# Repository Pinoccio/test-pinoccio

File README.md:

pinoccio-test-harness
=====================

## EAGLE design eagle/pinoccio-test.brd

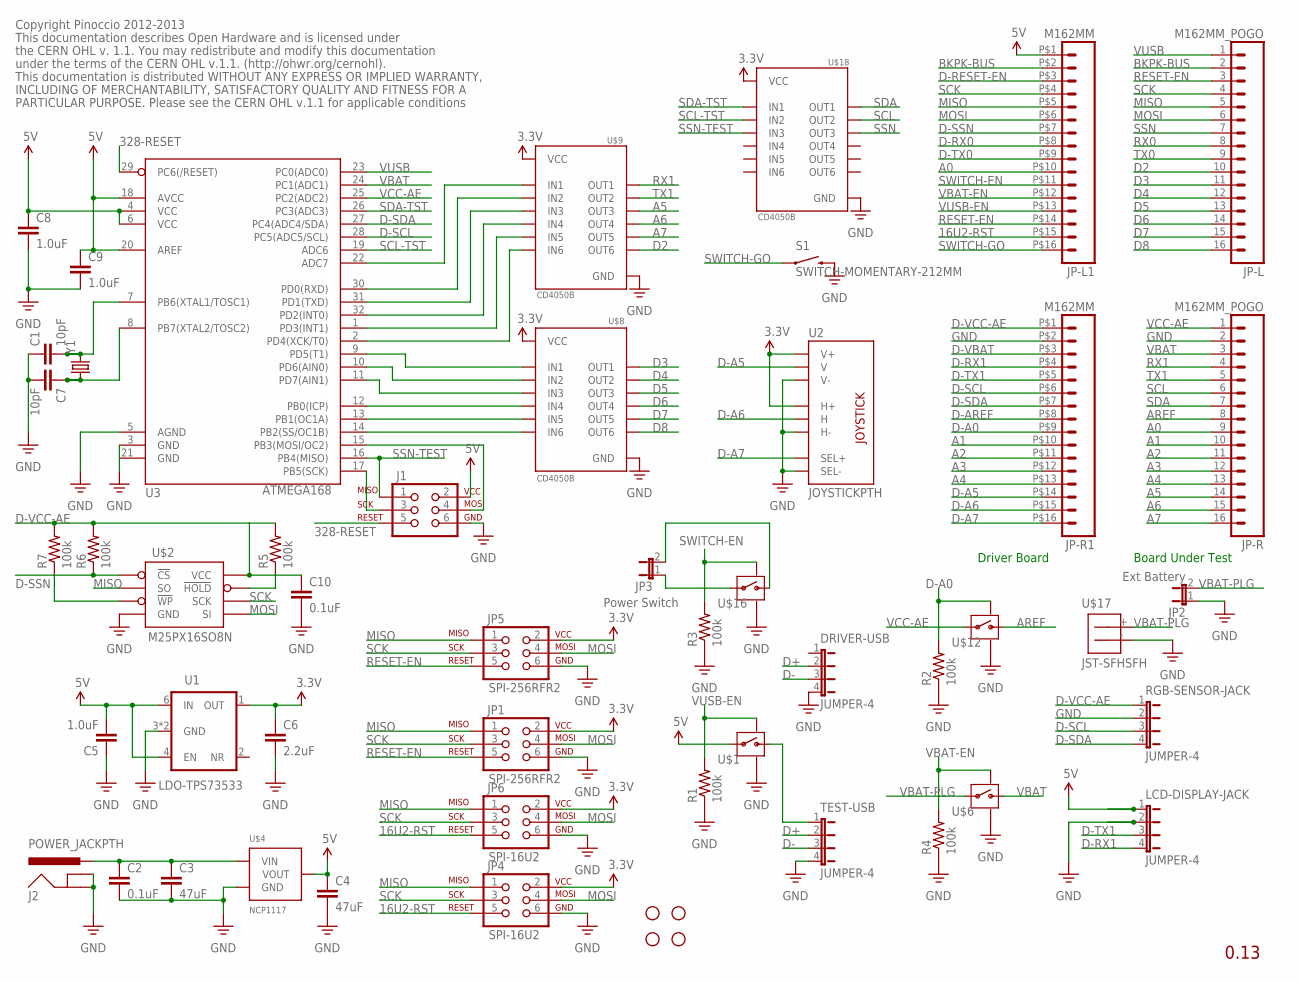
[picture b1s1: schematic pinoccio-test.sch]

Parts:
C1, C7: 10pF; 0402-CAP
C2, C10: 0.1uF; 0402-CAP
C3, C4: 47uF; 0805
C5, C8, C9: 1.0uF; 0402-CAP
C6: 2.2uF; 0402-CAP
DRIVER-USB: JUMPER-4; 1X04
J1: SPI-328P; 2X3
J2: POWER_JACKPTH; POWER_JACK_PTH
JP1, JP5: SPI-256RFR2; 2X3
JP2: Ext Battery; 1X02
JP3: Power Switch; 1X02
JP4, JP6: SPI-16U2; 2X3
JP7, JP9, JP10, JP12: STAND-OFF
JP-L: M162MM_POGO; 1X16_2MM_POGO
JP-L1: M162MM; 1X16_2MM
JP-R: M162MM_POGO; 1X16_2MM_POGO
JP-R1: M162MM; 1X16_2MM
LCD-DISPLAY-JACK: JUMPER-4; 1X04
R1, R2, R3, R4, R5, R6, R7: 100k; 0402-RES
RGB-SENSOR-JACK: JUMPER-4; 1X04
S1: SWITCH-MOMENTARY-212MM; TACTILE-PTH-12MM
TEST-USB: JUMPER-4; 1X04
U1: LDO-TPS73533; SON-6-DRV
U2: JOYSTICKPTH; JOYSTICK
U3: ATMEGA168; TQFP32-08
U$1, U$6, U$12, U$16: SWITCH-MOSFETTDFN4; TDFN4
U$2: M25PX16SO8N; SO8N
U$4: NCP1117; SOT223
U$8, U$9, U$18: CD4050B; TSSOP-16
U$17: JST-SFHSFH; JST-SFH
Y1: CRYSTALABM10; CRYSTAL-SMD-2.5X2-ABM10

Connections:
3.3V: C6.1, JP1.2, JP4.2, JP5.2, JP6.2, U1.1 (OUT), U2.H1 (H+), U2.V1 (V+), U$8.1 (VCC), U$9.1 (VCC), U$18.1 (VCC)
5V: C4.1, C5.2, C8.1, C9.1, J1.2, JP-L1.P$1 (1), LCD-DISPLAY-JACK.1, U1.4 (EN), U1.6 (IN), U3.4 (VCC), U3.6 (VCC), U3.18 (AVCC), U3.20 (AREF), U$1.P$3 (IN), U$4.2 (VOUT), U$4.4 (VOUT)
16U2-RST: JP4.5, JP6.5, JP-L1.P$15 (15)
328-RESET: J1.5, U3.29 (PC6(/RESET))
A0: JP-L1.P$10 (10), JP-R.9
A1: JP-R.10, JP-R1.P$10 (10)
A2: JP-R.11, JP-R1.P$11 (11)
A3: JP-R.12, JP-R1.P$12 (12)
A4: JP-R.13, JP-R1.P$13 (13)
A5: JP-R.14, U$9.6 (OUT3)
A6: JP-R.15, U$9.10 (OUT4)
A7: JP-R.16, U$9.12 (OUT5)
AREF: JP-R.8, U$12.P$1 (OUT)
BKPK-BUS: JP-L.2, JP-L1.P$2 (2)
D2: JP-L.10, U$9.15 (OUT6)
D3: JP-L.11, U$8.2 (OUT1)
D4: JP-L.12, U$8.4 (OUT2)
D5: JP-L.13, U$8.6 (OUT3)
D6: JP-L.14, U$8.10 (OUT4)
D7: JP-L.15, U$8.12 (OUT5)
D8: JP-L.16, U$8.15 (OUT6)
D+: DRIVER-USB.2, TEST-USB.2
D-: DRIVER-USB.3, TEST-USB.3
D-A0: JP-R1.P$9 (9), R2.2, U$12.P$4 (ON)
D-A5: JP-R1.P$14 (14), U2.V2 (V)
D-A6: JP-R1.P$15 (15), U2.H2 (H)
D-A7: JP-R1.P$16 (16), U2.B1A (SEL+)
D-AREF: JP-R1.P$8 (8)
D-RESET-EN: JP-L1.P$3 (3)
D-RX0: JP-L1.P$8 (8)
D-RX1: JP-R1.P$4 (4), LCD-DISPLAY-JACK.4
D-SCL: JP-R1.P$6 (6), RGB-SENSOR-JACK.3, U3.28 (PC5(ADC5/SCL))
D-SDA: JP-R1.P$7 (7), RGB-SENSOR-JACK.4, U3.27 (PC4(ADC4/SDA))
D-SSN: JP-L1.P$7 (7), R6.1, U$2.1 (!CS)
D-TX0: JP-L1.P$9 (9)
D-TX1: JP-R1.P$5 (5), LCD-DISPLAY-JACK.3
D-VBAT: JP-R1.P$3 (3)
D-VCC-AE: C10.1, JP-R1.P$1 (1), R5.2, R6.2, R7.2, RGB-SENSOR-JACK.1, U$2.8 (VCC)
GND: C1.1, C2.2, C3.2, C4.2, C5.1, C6.2, C7.2, C8.2, C9.2, C10.2, DRIVER-USB.4, J1.6, J2.GND, J2.GNDBREAK, JP1.6, JP2.1, JP4.6, JP5.6, JP6.6, JP-R.2, JP-R1.P$2 (2), LCD-DISPLAY-JACK.2, R1.1, R2.1, R3.1, R4.1, RGB-SENSOR-JACK.2, S1.3 (2), TEST-USB.4, U1.3 (GND), U1.PAD (GND), U2.B2A (SEL-), U2.H3 (H-), U2.V3 (V-), U3.3 (GND), U3.5 (AGND), U$1.P$2 (GND), U$1.P$5 (GND), U$2.4 (GND), U$4.1 (GND), U$6.P$2 (GND), U$6.P$5 (GND), U$8.8 (GND), U$9.8 (GND), U$12.P$2 (GND), U$12.P$5 (GND), U$16.P$2 (GND), U$16.P$5 (GND), U$17.-, U$18.8 (GND), Y1.P$2 (GND), Y1.P$4 (GND)
MISO: JP1.1, JP4.1, JP5.1, JP6.1, JP-L.5, JP-L1.P$5 (5), U$2.2 (SO)
MOSI: JP1.4, JP4.4, JP5.4, JP6.4, JP-L.6, JP-L1.P$6 (6), U$2.5 (SI)
unnamed: U3.2 (PD4(XCK/T0)), U$9.14 (IN6)
unnamed: U3.1 (PD3(INT1)), U$9.11 (IN5)
unnamed: U3.14 (PB2(SS/OC1B)), U$8.14 (IN6)
unnamed: C2.1, C3.1, J2.PWR, U$4.3 (VIN)
unnamed: U3.32 (PD2(INT0)), U$9.9 (IN4)
unnamed: C1.2, U3.7 (PB6(XTAL1/TOSC1)), Y1.P$3 (2)
unnamed: U3.31 (PD1(TXD)), U$9.7 (IN3)
unnamed: U3.13 (PB1(OC1A)), U$8.11 (IN5)
unnamed: U3.30 (PD0(RXD)), U$9.5 (IN2)
unnamed: U3.22 (ADC7), U$9.3 (IN1)
unnamed: U3.12 (PB0(ICP)), U$8.9 (IN4)
unnamed: JP3.2, U$16.P$1 (OUT)
unnamed: U3.11 (PD7(AIN1)), U$8.7 (IN3)
unnamed: C7.1, U3.8 (PB7(XTAL2/TOSC2)), Y1.P$1 (1)
unnamed: JP3.1, U$16.P$3 (IN)
unnamed: TEST-USB.1, U$1.P$1 (OUT)
unnamed: R7.1, U$2.3 (!WP)
unnamed: R5.1, U$2.7 (!HOLD)
unnamed: U3.10 (PD6(AIN0)), U$8.5 (IN2)
unnamed: U3.9 (PD5(T1)), U$8.3 (IN1)
unnamed: J1.4, U3.15 (PB3(MOSI/OC2))
unnamed: J1.3, U3.17 (PB5(SCK))
RESET-EN: JP1.5, JP5.5, JP-L.3, JP-L1.P$14 (14)
RX0: JP-L.8
RX1: JP-R.4, U$9.2 (OUT1)
SCK: JP1.3, JP4.3, JP5.3, JP6.3, JP-L.4, JP-L1.P$4 (4), U$2.6 (SCK)
SCL: JP-R.6, U$18.4 (OUT2)
SCL-TST: U3.19 (ADC6), U$18.5 (IN2)
SDA: JP-R.7, U$18.2 (OUT1)
SDA-TST: U3.26 (PC3(ADC3)), U$18.3 (IN1)
SSN: JP-L.7, U$18.6 (OUT3)
SSN-TEST: J1.1, U3.16 (PB4(MISO)), U$18.7 (IN3)
SWITCH-EN: JP-L1.P$11 (11), R3.2, U$16.P$4 (ON)
SWITCH-GO: JP-L1.P$16 (16), S1.1
TX0: JP-L.9
TX1: JP-R.5, U$9.4 (OUT2)
VBAT: JP-R.3, U3.24 (PC1(ADC1)), U$6.P$1 (OUT)
VBAT-EN: JP-L1.P$12 (12), R4.2, U$6.P$4 (ON)
VBAT-PLG: JP2.2, U$6.P$3 (IN), U$17.+
VCC-AE: JP-R.1, U3.25 (PC2(ADC2)), U$12.P$3 (IN)
VUSB: JP-L.1, U3.23 (PC0(ADC0))
VUSB-EN: JP-L1.P$13 (13), R1.2, U$1.P$4 (ON)

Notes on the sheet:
0.13
Copyright Pinoccio 2012-2013
This documentation describes Open Hardware and is licensed under
the CERN OHL v. 1.1. You may redistribute and modify this documentation
under the terms of the CERN OHL v.1.1. (http://ohwr.org/cernohl).
This documentation is distributed WITHOUT ANY EXPRESS OR IMPLIED WARRANTY,
INCLUDING OF MERCHANTABILITY, SATISFACTORY QUALITY AND FITNESS FOR A
PARTICULAR PURPOSE. Please see the CERN OHL v.1.1 for applicable conditions
Driver Board
Board Under Test

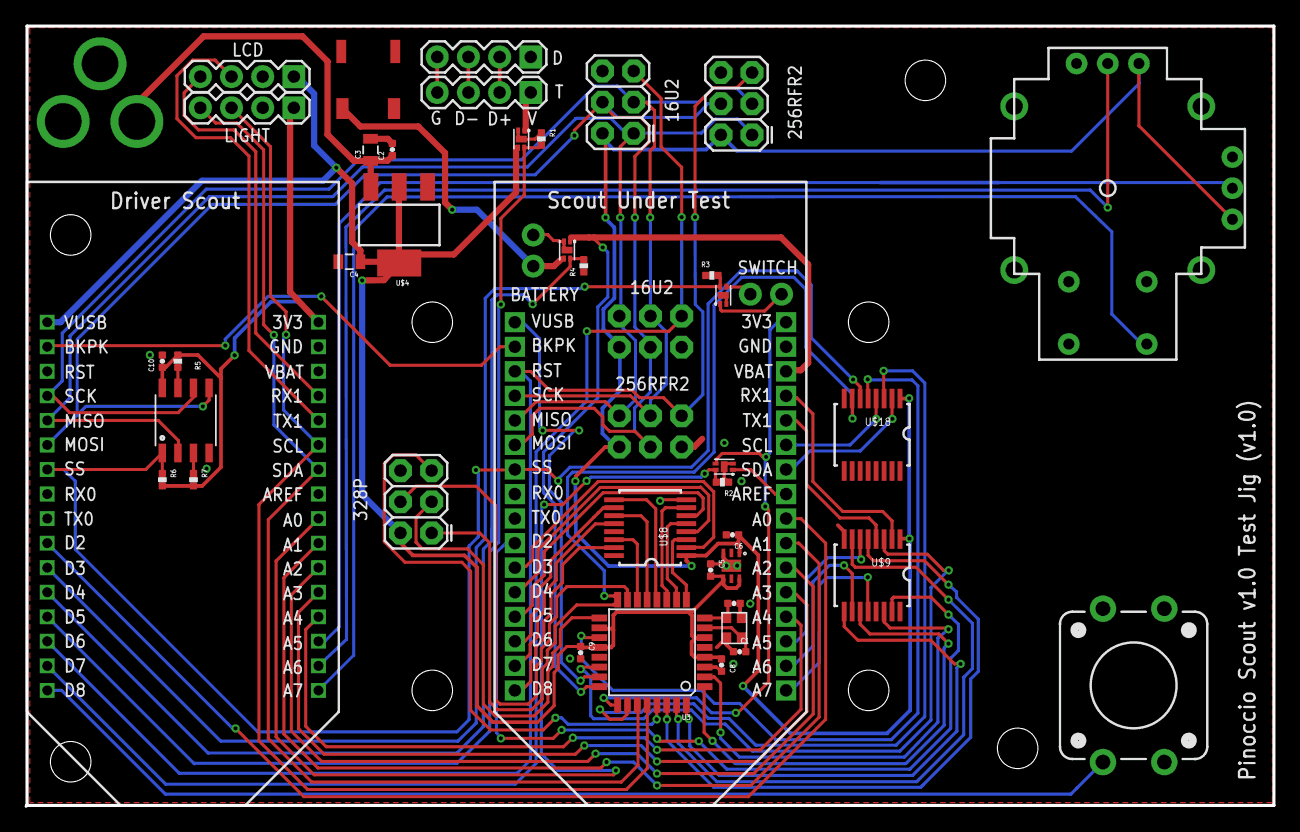
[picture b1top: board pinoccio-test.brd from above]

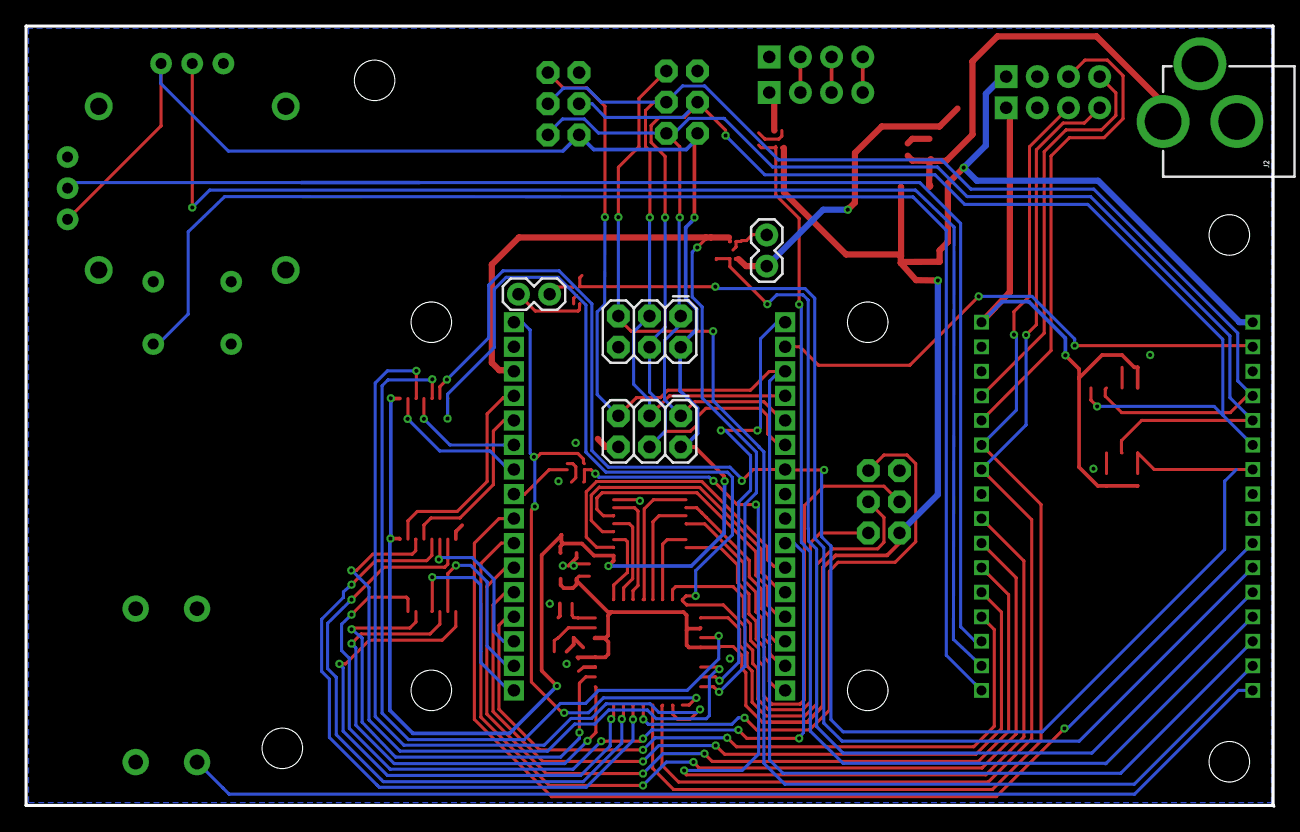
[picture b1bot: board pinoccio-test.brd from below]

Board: 2 copper layers, 101.7 x 63.6 mm, 56 parts (5 on the bottom side), 76 nets.

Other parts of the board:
JP8, JP11, JP13, JP14: STAND-OFF

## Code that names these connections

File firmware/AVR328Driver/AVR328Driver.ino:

/*
Set fuses to:
Low: FF (E2 for internal osc)
High: D1
Extended: FC
*/

#include <Wire.h>
#include <stdio.h>
#define VERSION "1.1"

//#define AVR_DEBUG
#ifdef AVR_DEBUG
#  define D(x) x
#else
#  define D(x)
#endif

enum {
  INIT,
  HANDSHAKE,
  DIGITAL_READ,
  DIGITAL_WRITE,
  ANALOG_READ,
  UNKNOWN
};

const char SLAVE_ADDR = 2;
char command = INIT;

// analog
#define VUSB   PC0  // A0 (D14)
#define VBAT   PC1  // A1 (D15)
#define VCC    PC2  // A2 (D16)

// digital
#define TX1_T  PD0  // D0
#define A5_T   PD1  // D1
#define A6_T   PD2  // D2
#define A7_T   PD3  // D3
#define D2_T   PD4  // D4
#define D3_T   PD5  // D5
#define D4_T   PD6  // D6
#define D5_T   PD7  // D7
#define D6_T   PB0  // D8
#define D7_T   PB1  // D9
#define D8_T   PB2  // D10
#define SSN_T  PB4  // D12
//#define SDA_T  PC3  // A3 (D17)
//#define SCL_T  ADC6 // A6 
//#define RX1_T  ADC7 // A7

char buffer[16];
int ctr;
char* output = (char *)malloc(256);
char out[8];
 
void setup() {
  for (int i=0; i<20; i++) {
    pinMode(i, OUTPUT);
    digitalWrite(i, LOW);
  }
  
  D(Serial.begin(115200));
  D(Serial.println("Starting up..."));
  
  Wire.begin(SLAVE_ADDR);          
  Wire.onReceive(receiveEvent);
  Wire.onRequest(requestEvent);
}

void loop() { }

// function that executes whenever data is received from master
// this function is registered as an event, see setup()
void receiveEvent(int howMany) {
  int pin;
  int value;
  ctr = 0;
  D(Serial.print("Received command: "));
  
  while (Wire.available()) { 
    buffer[ctr++] = Wire.read();
  }
  D(Serial.print(buffer));
  
  if (strncmp((const char*)buffer, "?", 1) == 0) {
    D(Serial.println(" (handshake)"));
    command = HANDSHAKE;
  } else if (strncmp((const char*)buffer, "RA", 2) == 0) {
    D(Serial.println(" (analogPinRead)"));
    command = ANALOG_READ;
  } else if (strncmp((const char*)buffer, "RD", 2) == 0) {
    D(Serial.println(" (digitalPinRead)"));
    command = DIGITAL_READ;
  } else if (strncmp((const char*)buffer, "WD", 2) == 0) {
    D(Serial.println(" (digitalPinWrite)"));
    command = DIGITAL_WRITE;
  } else {
    D(Serial.println(" (Unknown command)"));
    command = UNKNOWN;
    //Wire.write("bad command"); 
  }
}

// function that executes whenever data is requested by master
// this function is registered as an event, see setup()
void requestEvent() {
  char buf[3];
  buf[2] = 0;
  switch (command) {
    case HANDSHAKE:      
      handshake();
      break;
    case ANALOG_READ:
      buf[0] = buffer[ctr-1];
      analogPinRead(atoi(buf));
      break;
    case DIGITAL_READ:
      buf[0] = buffer[ctr-2];
      buf[1] = buffer[ctr-1];
      digitalPinRead(atoi(buf));
      break;
    case DIGITAL_WRITE:
      char buf2[3];
      buf2[0] = buffer[ctr-3];
      buf2[1] = buffer[ctr-2];
      buf2[2] = 0;
      buf[0] = buffer[ctr-1];
      digitalPinWrite(atoi(buf2), atoi(buf));
      break;
    case UNKNOWN:
      Wire.write("Unknown");
  }
}

void handshake() {
  D(Serial.print("Sending back "));
  D(Serial.print(VERSION));
  Wire.write(VERSION);
}

void analogPinRead(int pin) {
  D(Serial.print("Read A"));
  D(Serial.println(pin));

  uint16_t val = analogRead(pin);
  
  sprintf(output, ":%04u", val);
  
  D(Serial.print("Sending back: "));
  D(Serial.println(output));
  Wire.write(output);
}

void digitalPinRead(int pin) {
  pinMode(pin, INPUT);

  D(Serial.print("Read D"));
  D(Serial.print(pin));
  D(Serial.print(": "));
  D(Serial.println(digitalRead(pin)));
  
  sprintf(output, ":%01u", digitalRead(pin));
  
  D(Serial.print("Sending back: "));
  D(Serial.print(output));
  Wire.write(output);
  output[0] = 0;
}

void digitalPinWrite(int pin, int value) {
  D(Serial.print("Writing D"));
  D(Serial.print(pin));
  D(Serial.print(" to "));
  D(Serial.println(value));
  pinMode(pin, OUTPUT);
  digitalWrite(pin, value);
  
  D(Serial.println("Sending back: 1"));
  Wire.write(":1");
}

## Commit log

2013-10-16 Inital import
2013-10-27 Got i2c stuff talking between driver board and 328p
2013-10-27 Initialize all pins to 0
2013-10-28 Got all IO pin control working (except for the two that are ADC-only
2013-10-31 Add ATtiny13a bootloader to flash code
2013-10-31 Move flash programmer to its own class
2013-10-31 Fix #6: finish power supply testing
2013-11-07 Python serial writer to write hex to serial storage
2013-11-08 Got hex image in serial flash to write to 256RFR2 correctly
2013-11-08 another sketch try, no luck yet
2013-11-09 Add ability to read from any area of flash with readProgram()
2013-11-09 Add more debugging
2013-11-09 GOT IT WORKING MUTHAFUCKERS!
2013-11-09 Cleanup of testjig code
2013-11-10 More debug clenaup, got power completed, working on reset now
2013-11-13 Fix #4: gpio now is tested!
2013-11-27 Update GPIO tests to work better
2013-11-27 tightened up the 3V3 power checks
2013-11-27 Got close to having mesh done, couple loose ends
2013-11-28 Finished mesh test
2013-12-10 Update some of the unique ID/family/version EEPROM info
2013-12-13 Finalized test jig work
2013-12-20 Final fixups for test jig 1.0
2013-12-30 make longer timeout for 3V3 check, and explicitly reset the chip-select pins between chip flashes
2014-02-17 Include GS.h from PinoccioTestSuite sketch
    The pinoccio-arduino-library depends on the GS library, but the IDE
    doesn't know how to automatically include it in the build yet.
2014-02-17 Include string.h from md5.c for memcpy
    This prevents a compiler warning
2014-02-18 Adjust timeout timing issues
2014-02-18 Fix remaining disableShell issue
2014-04-14 Don't write the upper two bits of the 256RFR2 lock byte
    These bytes are reserved and they always read as 0. Better to write them
    as 0 too, to prevent confusing over what the correct value should be.
2014-06-06 Clean up SPI chip select
2014-06-06 Add multiple checks for 3.3v for sag
2014-06-06 More stable testing and update for latest Pinoccio library
2014-06-06 Fix up some brokenness in the test firmware
2014-06-06 Update bootstrap to 2014060501
2014-06-11 Add addl serial numbers for new jigs
2014-06-11 Loosen up prompt checking from being so strict
2016-09-20 Added adjustment of VUSB gate pin to handle the new p-channel mosfet which requires an active-low to enable
2016-09-20 Cleaned up SPI comms between calls to prevent a hung bus

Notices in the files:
eagle/pinoccio-test.brd:
Licensed under CERN OHL v.1.1
